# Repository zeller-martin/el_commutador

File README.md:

# el_commutador

a simple design for an active coaxial commutator with SMA connectors. used for tangle-free freely-moving neuronal recordings in small animals using ulca miniscopes or neuropixels probes. this design mainly differs from the design sold in the open ephys store in the follwowing aspects:
* mechanical parts and electronic controller are separate devices and connected with a cable
* use of a hollow-shaft stepper instead of a gear system decreases mechanical complexity and size of the device
* more simplistic and lower-priced design, but without any housing

# assembling the commutator

the file 'bom.xlsx' contains all necessary components. the file 'assembly.pdf' outlines the assembly of the hardware. the total cost of all components for a single commutator is ca. 300 euros.

# running the commutator

load the script 'motor_teensy.ino' onto the teensy 4.0 using arduino software with teensyduino software. the file 'el_commutador.py' contains the function 'run_commutator' to launch a GUI instance for a commutator. for now we feed real-time head direction information into the system by reading the head orientation .csv-file as it is written by the miniscope recording software. in the future other sources of head direction data can be implemented to be fed in the GUI. manual operation is also possible.

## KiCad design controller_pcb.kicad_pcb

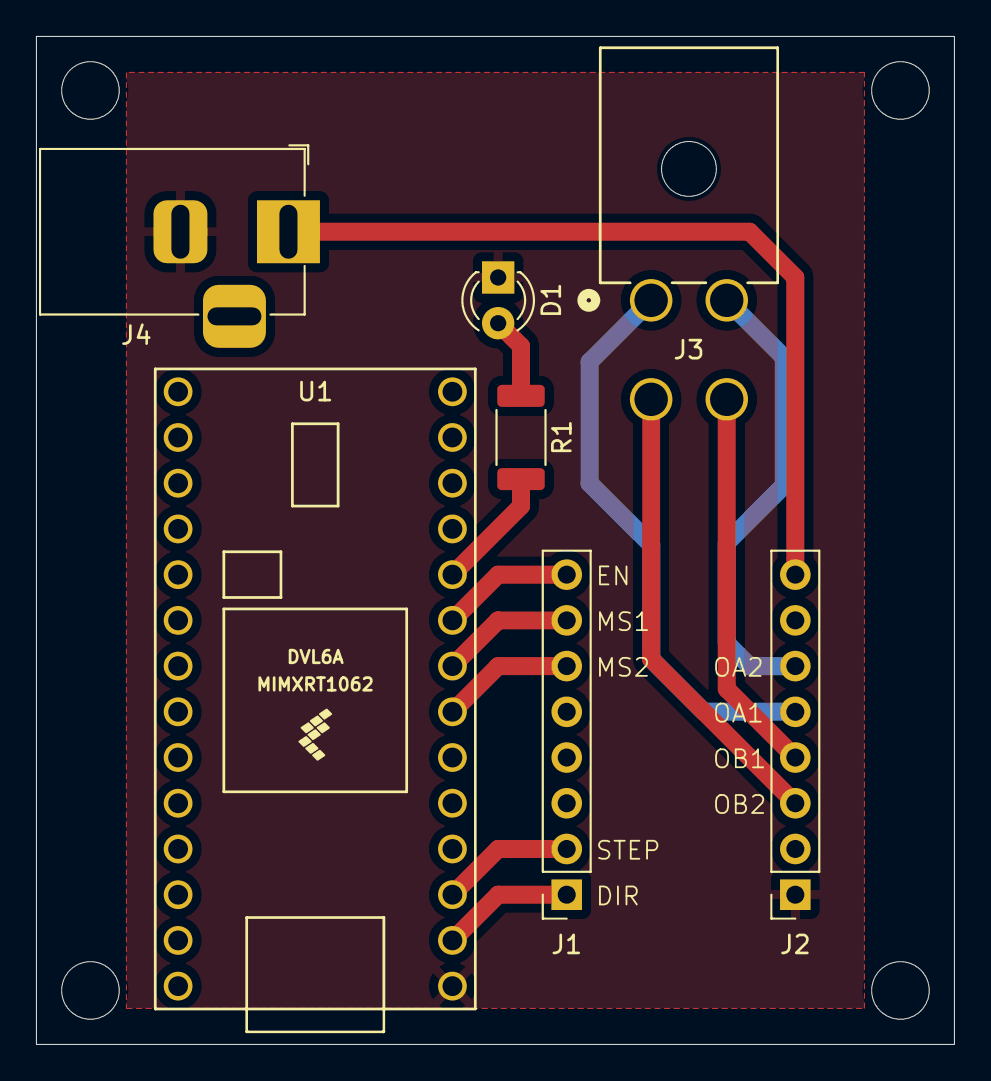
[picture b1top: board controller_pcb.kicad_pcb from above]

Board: 2 copper layers, 51.0 x 56.0 mm, 7 parts (0 on the bottom side), 13 nets.

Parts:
D1: LED; LED_D3.0mm
J1, J2: Conn_01x08_Socket; PinSocket_1x08_P2.54mm_Vertical
J3: 26013115; CONN_5569-04A_MOL
J4: Barrel_Jack_MountingPin; BarrelJack_Horizontal
R1: R; R_2010_5025Metric
U1: Teensy4.0; Teensy40

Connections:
unnamed: D1.2 (A), R1.1
unnamed: D1.1 (K), J2.1, J4.2, U1.1 (GND)
unnamed: J1.1, U1.2 (0_RX1_CRX2_CS1)
unnamed: J1.2, U1.3 (1_TX1_CTX2_MISO1)
unnamed: J1.6, U1.7 (5_IN2)
unnamed: J1.7, U1.8 (6_OUT1D)
unnamed: J1.8, U1.9 (7_RX2_OUT1A)
unnamed: J2.3, J3.3
unnamed: J2.4, J3.4
unnamed: J2.5, J3.1
unnamed: J2.6, J3.2
unnamed: J2.8, J4.1
unnamed: R1.2, U1.10 (8_TX2_IN1)

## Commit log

2025-04-15 add files for commutator construction
2025-04-15 added specifications for plexiglass plate
2025-04-15 update bon
2025-04-15 typo
2025-04-15 change sense
2025-04-16 add pinging functionality
2025-04-20 remove unused pin
2025-06-10 added assembly manual
2025-06-10 Update README.md with cost estimate
